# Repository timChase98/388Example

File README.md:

# ECE 388 Board Submission Standards

## Directory Layout
In the base Directory should be your Kicad project files and a directory called "renders" which contains the output files from your project. If you want to also version control your firmware (which you probably should) you can have a folder called "firmware" to manage code.  You must also have the gitignore that came with your repo.  

Your repo should be well maintained and updated regularly.  I should not just see a single commit titled "done".  You should be making frequent commits as you make changes to the status of your project.  You should also regularly push.

## README
The readme for your project should contain your project title, an overview of your project and any additionally relevant information. Images may go into the readmeimg folder. You must have the DRC badge present below your project title for submissions to be graded.

## Automated ERC and DRC Checks
Your repository has been configured to automatically run an ERC and DRC every time you push. Both of the ERC and DRC need to pass for a submission to be accepted. This will be signified by a green passing badge in the readme.

## Kicad Library
The whole class will share a kicad library on GitHub. The repo can be found [HERE](https://github.com/UmassD-ECE388/388Lib). You should fork this repo (information about forks [HERE](https://docs.github.com/en/github/collaborating-with-pull-requests/working-with-forks)), clone your fork onto your local machine and add both the symbol and footprints libraries to your library manager in Kicad.

From your project view select Preferences->Manage Symbol Libraries then click the add existing library button and navigate to where you cloned your fork of 388Lib to. Repeat these steps for Preferences->Manage Footprint Libraries

 Any symbols or footprints needed for your project need to be added to your local fork of the repo and shared with the class by submitting a pull request to the upstream repo. You are responsible for learning how to do this. There is plenty of documentation online (including some linked in this readme) about how to do this.

**ALL symbols and footprints used in your project need to be in the 388Lib repo before grading**

## Submissions
Submissions should be in the form of GitHub Releases.  When a deadline comes around whatever the latest release on your repo is will be taken as your submission.  You should not email me submissions, email submissions will not be graded.  Each submission must have a unique tag number starting X.00 where X is the number associated with the submission. When asked to resubmit you should increment the minor version number of the tag. EX if you just submitted with a tag of v1.00 the first resubmission should be tagged v1.01, the 10th resubmission would be v1.10. The hundredth submission should be taken as a sign that it's time revaluate some things.

Documentation on how to create a release can be found [HERE](https://docs.github.com/en/free-pro-team@latest/github/administering-a-repository/managing-releases-in-a-repository).

## Schematics Submission
You will create a release called "Schematic Submission" with an initial tag of v1.00

ERC must be run on all schematic before submission.  ERC errors will not only make your board not work, it will also make your design get rejected.  Schematics should be submitted as a PDF located in the "renders" folder.  To get Kicad to produce a PDF of your schematic select the plotter icon from the top menu and select the following settings.  

It's important that if you have more than one page that you select to export all pages.

## Bill Of Materials Submission
You will create a release titled "BOM Submission" with an initial tag of v2.00

We will be using [LCSC](https://lcsc.com) as our preferred supplier.  As such, all parts should be sourceable from LCSC unless previously discussed with myself.  Once submitted each group will meet with me for a Bill Of Materials (BOM) review.  BOM's should be exported from Kicad, then all additional data needs to be added. To do this in Eeschema go to Tools -> Generate Bill Of Materials and select bom2grouped_csv.  This will generate the BOM is Comma Separated Variable format.

After Kicad generates a BOM file you need to open it in a CSV editor of your choice, excel, open office, atom if you're a cool kid, vscode if you're a nerd, and patch in the additional data needed to submit.  This includes price breakdowns, LCSC part numbers and links.  An example is provided in this repository.  If a part is not available from LCSC and you have discussed this with me you can enter data into the OTHER SUPPLIER fields, otherwise they are unnecessary.  Note price breakdowns are for the cost of 1 part at the listed quantity, not the extended price.  

**BOMs That do not meet the format specification will be rejected** This means they must have all of the correct columns, in the correct order, with correct data in them, and be in **CSV** format.  

**All parts necessary for production of you board must be on the BOM** this included displays, connectors, wiring, etc.  If you need it for your board to be functional it needs to be on the BOM. Components that are not physical parts, ex mounting holes, fiducials, etc, should not be included.  

**We are ordering parts from LCSC.  BOMs that do not have LSCS part numbers will be rejected**

## Board Layout
It is important that the first thing you do when you start to layout your board is to setup your DRCs.  DRCs are the minimum checks you can do to make sure your board will have the possibility of being manufacturable.  They do not however verify your board will work correctly.  

We will be using JLCPCB's prototyping service for board production.  JLCPCB's design minimum design rules are located [HERE](https://jlcpcb.com/capabilities/Capabilities). **Some of these rules are different for different board configurations** unless you have specifically discussed with me your board will be 2 layer 1oz copper on 1.6mm FR-4.  Note these are minimums, not recommend values.  You should use Kicad's built-in circuit board calculator to come up with minimum for high power or critical traces.  All of these things need to be configured in the board setup dialog accessible via File -> Board Setup

It is also important to take note of silkscreen (called legend on the JLCPCB website) minimums.  A lot of standard libraries come with small text sizes and will need to be increased to pass DRC.  This can be done by setting the text properties in the Board Setup dialog.

Then going to Edit -> Text and Graphics properties and settings the following settings

Additionally it can be useful to have the help of the interactive router.  This is entirely up to personal preference, my preferred settings are shown below.  This dialog is accessible via the Route -> Interactive Router Settings menu.

Periodically while laying out your board you should run a DRC to verify there are no manufacturing issues. It is sometimes ok to wave DRC errors as Approved.  If there is an error that you believe should be waved discuss this with Dr. Viall or myself before continuing.

To verify you read this put a text file in the Renders folder titled "verification.txt" that contains the line "No Green M&M's were harmed in the production of this board" and nothing else.  Do not discuss this with requirement with other groups. 

## Board Submission
You will create a release called "Gerber Submission" with an initial tag of v3.00

DRC must be run on your board prior to submitting.  Any unapproved DRC errors will result in your design being rejected.  
**Boards with critical DRC errors are unmanufacturable**

**Boards must be clearly marked with identifying information** This includes the product name, Revision, Date, Lead layout engineer, all group members names, and the link to the project GitHub.  An Example from a Senior Design project is included below.  

**Boards must have Fiducials for automated assembly.** Submissions that do not have 1mm fiducials in the bottom left (FID1), Top Right (FID2), and Top Left (FID3) will be rejected. Note the ordering of the three fiducials is important for automated assembly. The area around fiducials should be clear of components that may interfere with automatic recognition (i.e. mounting holes, pin headers etc.) for at least 3mm from any edge of the copper center.  

Boards will be submitted in the form of gerber files located in the renders/gerbers directory.   

Directions to generate Gerber Files can be found [HERE](https://support.jlcpcb.com/article/149-how-to-generate-gerber-and-drill-files-in-kicad)

**You must generate both gerber and drill files to get your board manufactured**

## Board Population

In order to get a board assembled through the automated assembly process you must submit a finalized BOM that includes quantities and UUIDs from the stock sheet [HERE](https://docs.google.com/spreadsheets/d/1WtOakf2sV2Z24B9SvWYXxpJuLNhJUgvYpcEkdbbXuQU/edit#gid=0) and designators.  If a component is being sourced by you rather than a part that was ordered from the BOM you should put a "Y" in the self sourced column.  This file should only reflect components that need to be populated on the board.  i.e. resistors, caps, ICs, not mounting holes or solder jumpers.  An example of this is attached can be seen in this repo.  It should be named yourProjectName_assembly.csv and be in the base directory of your project when you create an assembly release.  Once you have submitted this file and your Kicad project files are in the repo you can schedule an appointment to get your board assembled.  

## Feedback

Feedback will be provided via Github Issues.  Changes that need to be made will be listed as a series of checkboxes on an issue.  These boxes should be checked off as they are completed.  You should have all of the boxes check before closing the issue to notify me that your submission needs to be reevaluated.  Any discussion about submissions should be done on the issue page.

**I can not recommend strongly enough that you have everything in as early as possible.  Your designs will likely get rejected the first time and you need time to be able to get a manufacturable board in before the deadline to order.**

## Relevant Links

[Layout Video](https://www.youtube.com/watch?v=Pfe_roicJkg)

[388Lib](https://github.com/UmassD-ECE388/388Lib)

[Stock Sheet](https://docs.google.com/spreadsheets/d/1WtOakf2sV2Z24B9SvWYXxpJuLNhJUgvYpcEkdbbXuQU/)

[PCB House](https://jlcpcb.com/)

[Component Supplier](https://lcsc.com/)

[AVR Hardware Implementation](http://ww1.microchip.com/downloads/en/AppNotes/AN2519-AVR-Microcontroller-Hardware-Design-Considerations-00002519B.pdf)

[AVR I2C](https://www.microchip.com/en-us/application-notes/an2480)

[NXP I2C Level Shifter](https://cdn-shop.adafruit.com/datasheets/an97055.pdf)

[TI Reverse Voltage Protection](https://www.ti.com/lit/an/slva139/slva139.pdf?ts=1632762332598&ref_url=https%253A%252F%252Fwww.google.com%252F)

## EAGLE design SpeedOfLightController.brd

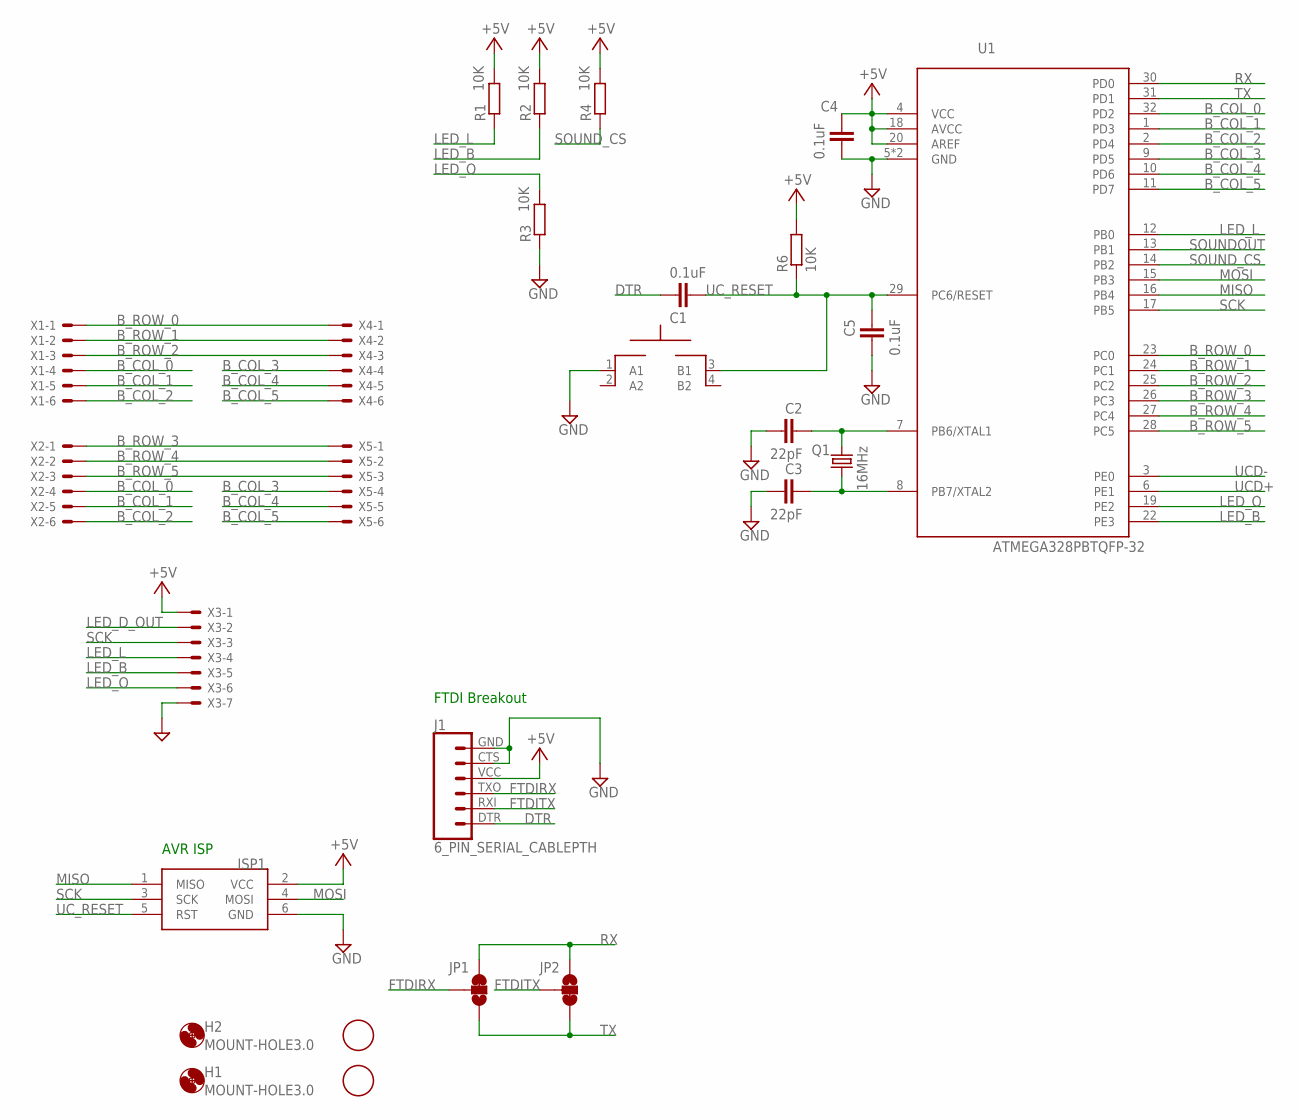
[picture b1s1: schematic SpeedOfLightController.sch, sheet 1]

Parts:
AF1, AF2: FIDUCIAL; FIDUCIAL_1MM
C1, C4, C5: 0.1uF; C0805
C2, C3: 22pF; C0805
H1, H2: MOUNT-HOLE3.0; 3,0
ISP1: AVRISP-6; AVRISP
J1: 6_PIN_SERIAL_CABLEPTH; FTDI_BASIC
JP1, JP2: JUMPER-SMT_3_1-NC_TRACE_SILK; SMT-JUMPER_3_1-NC_TRACE_SILK
Q1: 16MHz; HC49UP
R1, R2, R3, R4, R6: 10K; R0805
RESET: MOMENTARYBUTTON; SPST_NO_SMD
U1: ATMEGA328PBTQFP-32; QFP80P900X900X120-32N
X1, X2, X4, X5: JST-XH-06-PIN-LONG-PAD; JST-XH-06-PACKAGE-LONG-PAD
X3: JST-XH-07-PIN-LONG-PAD; JST-XH-07-PACKAGE-LONG-PAD

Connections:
+5V: C4.2, ISP1.2 (VCC), J1.VCC (4), R1.2, R2.2, R4.2, R6.2, U1.4 (VCC), U1.18 (AVCC), U1.20 (AREF), X3.1; also elsewhere on the board
B_COL_0: U1.32 (PD2), X1.4, X2.4
B_COL_1: U1.1 (PD3), X1.5, X2.5
B_COL_2: U1.2 (PD4), X1.6, X2.6
B_COL_3: U1.9 (PD5), X4.4, X5.4
B_COL_4: U1.10 (PD6), X4.5, X5.5
B_COL_5: U1.11 (PD7), X4.6, X5.6
B_ROW_0: U1.23 (PC0), X1.1, X4.1
B_ROW_1: U1.24 (PC1), X1.2, X4.2
B_ROW_2: U1.25 (PC2), X1.3, X4.3
B_ROW_3: U1.26 (PC3), X2.1, X5.1
B_ROW_4: U1.27 (PC4), X2.2, X5.2
B_ROW_5: U1.28 (PC5), X2.3, X5.3
DTR: C1.2, J1.DTR (1)
FTDIRX: J1.TXO (3), JP1.2
FTDITX: J1.RXI (2), JP2.2
GND: C2.1, C3.1, C4.1, C5.1, ISP1.6 (GND), J1.CTS (5), J1.GND (6), R3.1, RESET.1 (A1), U1.5 (GND), U1.21 (GND), X3.7; also elsewhere on the board
LED_B: R2.1, U1.22 (PE3), X3.5; also elsewhere on the board
LED_D_OUT: X3.2; also elsewhere on the board
LED_L: R1.1, U1.12 (PB0), X3.4; also elsewhere on the board
LED_O: R3.2, U1.19 (PE2), X3.6; also elsewhere on the board
MISO: ISP1.1 (MISO), U1.16 (PB4); also elsewhere on the board
MOSI: ISP1.4 (MOSI), U1.15 (PB3); also elsewhere on the board
unnamed: C2.2, Q1.1, U1.7 (PB6/XTAL1)
unnamed: C3.2, Q1.2, U1.8 (PB7/XTAL2)
RX: JP1.3, JP2.1, U1.30 (PD0)
SCK: ISP1.3 (SCK), U1.17 (PB5), X3.3; also elsewhere on the board
SOUNDOUT: U1.13 (PB1); also elsewhere on the board
SOUND_CS: R4.1, U1.14 (PB2); also elsewhere on the board
TX: JP1.1, JP2.3, U1.31 (PD1)
UCD+: U1.6 (PE1); also elsewhere on the board
UCD-: U1.3 (PE0); also elsewhere on the board
UC_RESET: C1.1, C5.2, ISP1.5 (RST), R6.1, RESET.3 (B1), U1.29 (PC6/RESET)

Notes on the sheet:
AVR ISP
FTDI Breakout

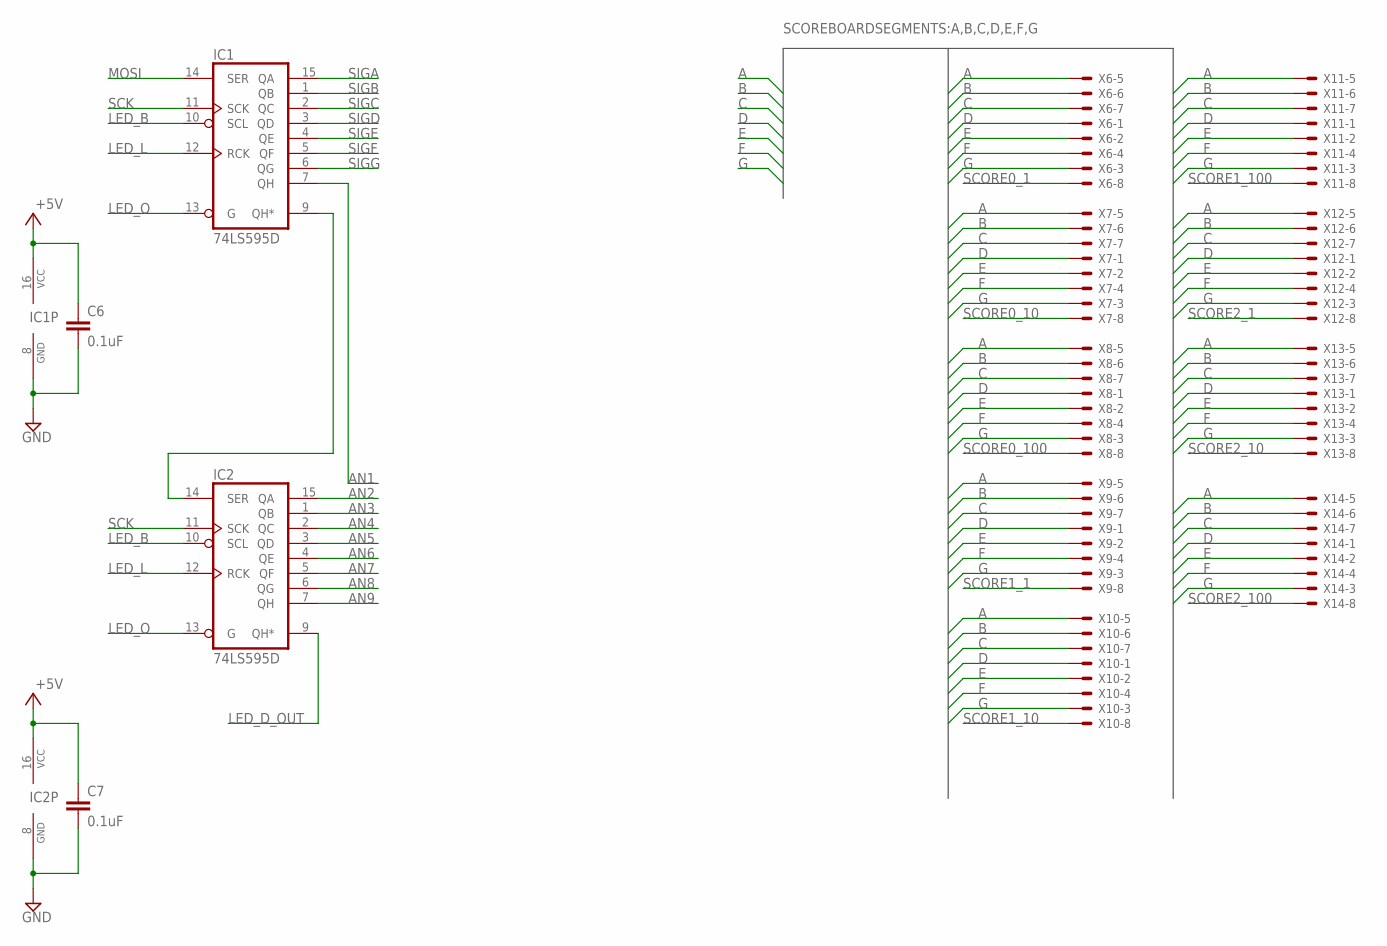
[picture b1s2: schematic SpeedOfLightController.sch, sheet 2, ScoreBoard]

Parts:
C6, C7: 0.1uF; C0805
IC1, IC2: 74LS595D; SO16
X6, X7, X8, X9, X10, X11, X12, X13, X14: JST-XH-08-PIN-LONG-PAD; JST-XH-08-PACKAGE-LONG-PAD

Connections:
+5V: C6.1, C7.1, IC1.16 (VCC), IC2.16 (VCC); also elsewhere on the board
A: X6.5, X7.5, X8.5, X9.5, X10.5, X11.5, X12.5, X13.5, X14.5; also elsewhere on the board
AN1: IC1.7 (QH); also elsewhere on the board
AN2: IC2.15 (QA); also elsewhere on the board
AN3: IC2.1 (QB); also elsewhere on the board
AN4: IC2.2 (QC); also elsewhere on the board
AN5: IC2.3 (QD); also elsewhere on the board
AN6: IC2.4 (QE); also elsewhere on the board
AN7: IC2.5 (QF); also elsewhere on the board
AN8: IC2.6 (QG); also elsewhere on the board
AN9: IC2.7 (QH); also elsewhere on the board
B: X6.6, X7.6, X8.6, X9.6, X10.6, X11.6, X12.6, X13.6, X14.6; also elsewhere on the board
C: X6.7, X7.7, X8.7, X9.7, X10.7, X11.7, X12.7, X13.7, X14.7; also elsewhere on the board
D: X6.1, X7.1, X8.1, X9.1, X10.1, X11.1, X12.1, X13.1, X14.1; also elsewhere on the board
E: X6.2, X7.2, X8.2, X9.2, X10.2, X11.2, X12.2, X13.2, X14.2; also elsewhere on the board
F: X6.4, X7.4, X8.4, X9.4, X10.4, X11.4, X12.4, X13.4, X14.4; also elsewhere on the board
G: X6.3, X7.3, X8.3, X9.3, X10.3, X11.3, X12.3, X13.3, X14.3; also elsewhere on the board
GND: C6.2, C7.2, IC1.8 (GND), IC2.8 (GND); also elsewhere on the board
LED_B: IC1.10 (SCL), IC2.10 (SCL); also elsewhere on the board
LED_D_OUT: IC2.9 (QH*); also elsewhere on the board
LED_L: IC1.12 (RCK), IC2.12 (RCK); also elsewhere on the board
LED_O: IC1.13 (G), IC2.13 (G); also elsewhere on the board
MOSI: IC1.14 (SER); also elsewhere on the board
unnamed: IC1.9 (QH*), IC2.14 (SER)
SCK: IC1.11 (SCK), IC2.11 (SCK); also elsewhere on the board
SCORE0_1: X6.8; also elsewhere on the board
SCORE0_10: X7.8; also elsewhere on the board
SCORE0_100: X8.8; also elsewhere on the board
SCORE1_1: X9.8; also elsewhere on the board
SCORE1_10: X10.8; also elsewhere on the board
SCORE1_100: X11.8; also elsewhere on the board
SCORE2_1: X12.8; also elsewhere on the board
SCORE2_10: X13.8; also elsewhere on the board
SCORE2_100: X14.8; also elsewhere on the board
SIGA: IC1.15 (QA); also elsewhere on the board
SIGB: IC1.1 (QB); also elsewhere on the board
SIGC: IC1.2 (QC); also elsewhere on the board
SIGD: IC1.3 (QD); also elsewhere on the board
SIGE: IC1.4 (QE); also elsewhere on the board
SIGF: IC1.5 (QF); also elsewhere on the board
SIGG: IC1.6 (QG); also elsewhere on the board

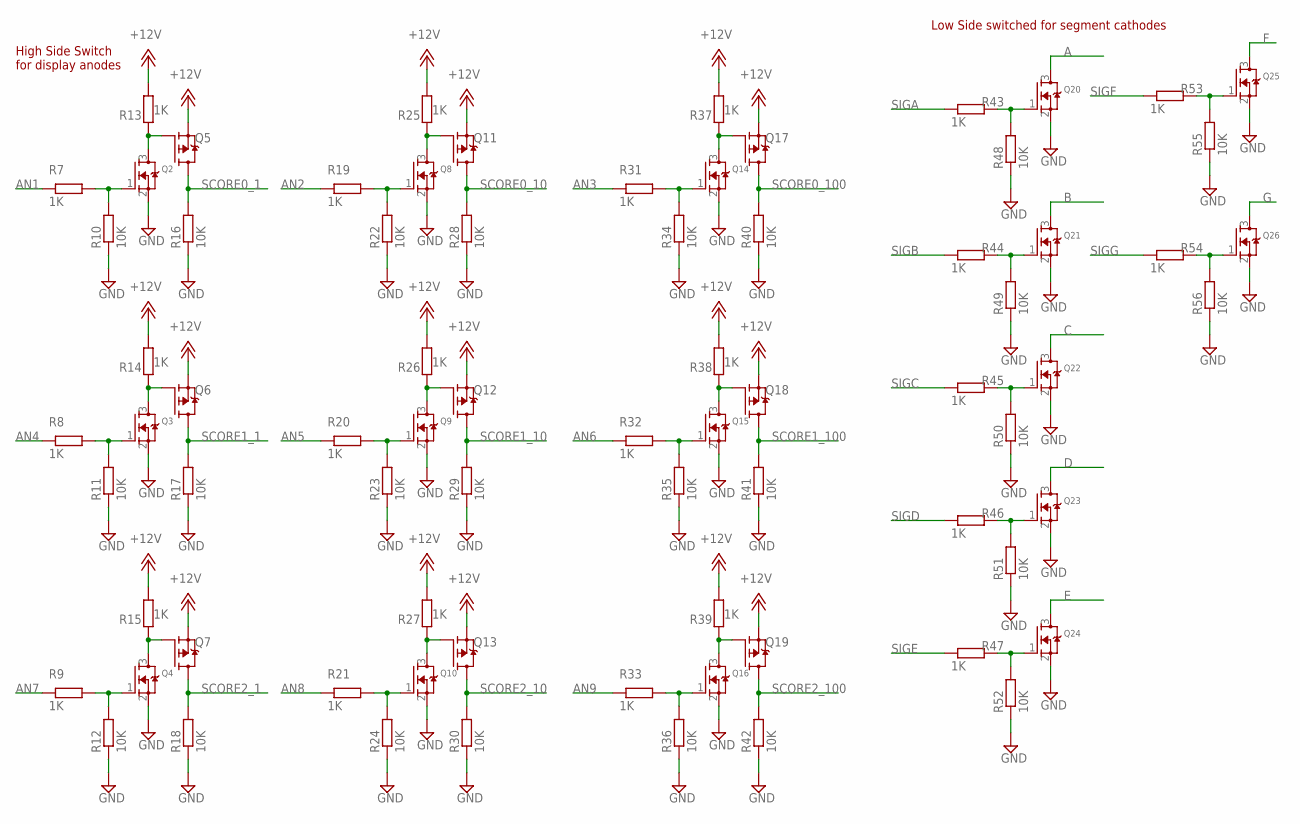
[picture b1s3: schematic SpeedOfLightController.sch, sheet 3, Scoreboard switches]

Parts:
Q2, Q3, Q4, Q8, Q9, Q10, Q14, Q15, Q16, Q20, Q21, Q22, Q23, Q24, Q25, Q26: AO3414SOT23; SOT95P240X110-3N
Q5, Q6, Q7, Q11, Q12, Q13, Q17, Q18, Q19: AO3415; SOT95P240X110-3N
R7, R8, R9, R13, R14, R15, R19, R20, R21, R25, R26, R27, R31, R32, R33, R37, R38, R39, R43, R44, R45, R46, R47, R53, R54: 1K; R0805
R10, R11, R12, R16, R17, R18, R22, R23, R24, R28, R29, R30, R34, R35, R36, R40, R41, R42, R48, R49, R50, R51, R52, R55, R56: 10K; R0805

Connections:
+12V: Q5.2 (S), Q6.2 (S), Q7.2 (S), Q11.2 (S), Q12.2 (S), Q13.2 (S), Q17.2 (S), Q18.2 (S), Q19.2 (S), R13.2, R14.2, R15.2, R25.2, R26.2, R27.2, R37.2, R38.2, R39.2; also elsewhere on the board
A: Q20.3 (D); also elsewhere on the board
AN1: R7.1; also elsewhere on the board
AN2: R19.1; also elsewhere on the board
AN3: R31.1; also elsewhere on the board
AN4: R8.1; also elsewhere on the board
AN5: R20.1; also elsewhere on the board
AN6: R32.1; also elsewhere on the board
AN7: R9.1; also elsewhere on the board
AN8: R21.1; also elsewhere on the board
AN9: R33.1; also elsewhere on the board
B: Q21.3 (D); also elsewhere on the board
C: Q22.3 (D); also elsewhere on the board
D: Q23.3 (D); also elsewhere on the board
E: Q24.3 (D); also elsewhere on the board
F: Q25.3 (D); also elsewhere on the board
G: Q26.3 (D); also elsewhere on the board
GND: Q2.2 (S), Q3.2 (S), Q4.2 (S), Q8.2 (S), Q9.2 (S), Q10.2 (S), Q14.2 (S), Q15.2 (S), Q16.2 (S), Q20.2 (S), Q21.2 (S), Q22.2 (S), Q23.2 (S), Q24.2 (S), Q25.2 (S), Q26.2 (S), R10.1, R11.1, R12.1, R16.1, R17.1, R18.1, R22.1, R23.1, R24.1, R28.1, R29.1, R30.1, R34.1, R35.1, R36.1, R40.1, R41.1, R42.1, R48.1, R49.1, R50.1, R51.1, R52.1, R55.1, R56.1; also elsewhere on the board
unnamed: Q21.1 (G), R44.2, R49.2
unnamed: Q22.1 (G), R45.2, R50.2
unnamed: Q23.1 (G), R46.2, R51.2
unnamed: Q24.1 (G), R47.2, R52.2
unnamed: Q20.1 (G), R43.2, R48.2
unnamed: Q25.1 (G), R53.2, R55.2
unnamed: Q26.1 (G), R54.2, R56.2
unnamed: Q2.1 (G), R7.2, R10.2
unnamed: Q8.1 (G), R19.2, R22.2
unnamed: Q14.1 (G), R31.2, R34.2
unnamed: Q3.1 (G), R8.2, R11.2
unnamed: Q9.1 (G), R20.2, R23.2
unnamed: Q15.1 (G), R32.2, R35.2
unnamed: Q4.1 (G), R9.2, R12.2
unnamed: Q10.1 (G), R21.2, R24.2
unnamed: Q16.1 (G), R33.2, R36.2
unnamed: Q16.3 (D), Q19.1 (G), R39.1
unnamed: Q10.3 (D), Q13.1 (G), R27.1
unnamed: Q4.3 (D), Q7.1 (G), R15.1
unnamed: Q3.3 (D), Q6.1 (G), R14.1
unnamed: Q9.3 (D), Q12.1 (G), R26.1
unnamed: Q15.3 (D), Q18.1 (G), R38.1
unnamed: Q14.3 (D), Q17.1 (G), R37.1
unnamed: Q8.3 (D), Q11.1 (G), R25.1
unnamed: Q2.3 (D), Q5.1 (G), R13.1
SCORE0_1: Q5.3 (D), R16.2; also elsewhere on the board
SCORE0_10: Q11.3 (D), R28.2; also elsewhere on the board
SCORE0_100: Q17.3 (D), R40.2; also elsewhere on the board
SCORE1_1: Q6.3 (D), R17.2; also elsewhere on the board
SCORE1_10: Q12.3 (D), R29.2; also elsewhere on the board
SCORE1_100: Q18.3 (D), R41.2; also elsewhere on the board
SCORE2_1: Q7.3 (D), R18.2; also elsewhere on the board
SCORE2_10: Q13.3 (D), R30.2; also elsewhere on the board
SCORE2_100: Q19.3 (D), R42.2; also elsewhere on the board
SIGA: R43.1; also elsewhere on the board
SIGB: R44.1; also elsewhere on the board
SIGC: R45.1; also elsewhere on the board
SIGD: R46.1; also elsewhere on the board
SIGE: R47.1; also elsewhere on the board
SIGF: R53.1; also elsewhere on the board
SIGG: R54.1; also elsewhere on the board

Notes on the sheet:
High Side Switch for display anodes
Low Side switched for segment cathodes

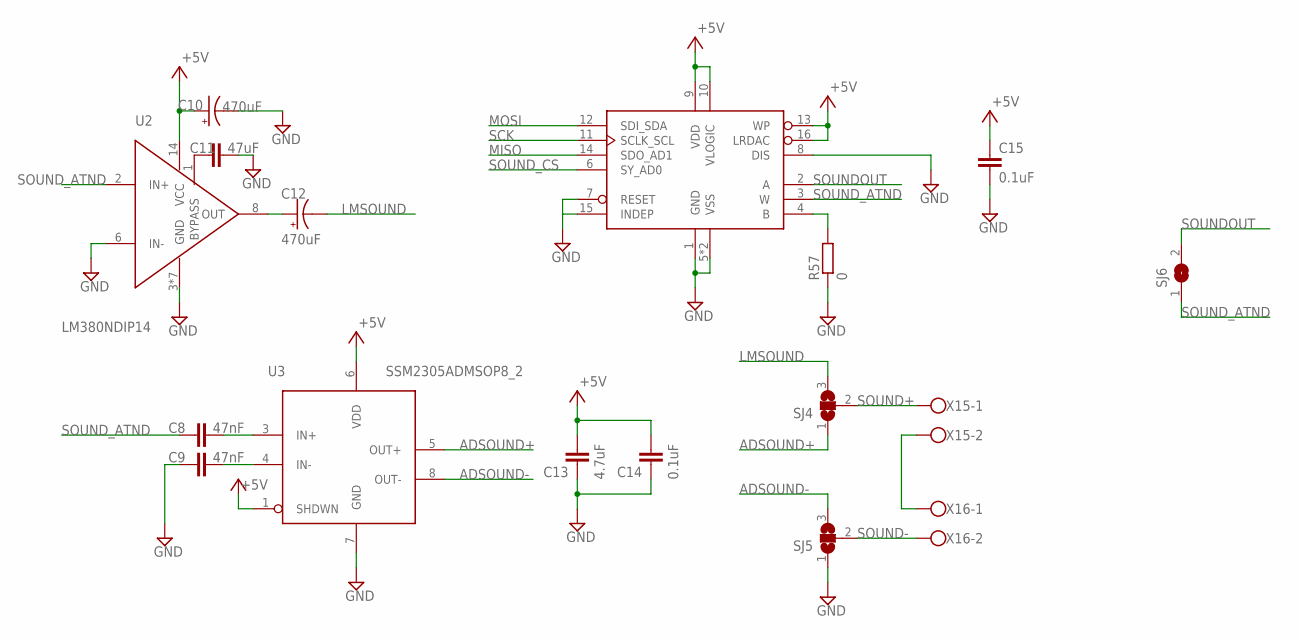
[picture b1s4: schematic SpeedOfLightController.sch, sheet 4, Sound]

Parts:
C8, C9: 47nF; C0805
C10, C12: 470uF; 140CLH-0810
C11: 47uF; C0805
C13: 4.7uF; C0805
C14, C15: 0.1uF; C0805
R57: 0; R0805W
SJ4, SJ5: SJ2W; SJ_2
SJ6: SJ
U2: LM380NDIP14; DIP762W53P254L1969H508Q14B
U3: SSM2305ADMSOP8_2; SOP65P490X95-8N
U4: AD5141ADLFCSP3; QFN50P300X300X80-17T160N
X15, X16: 1X02_5MM_SCREW; W237-102

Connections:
+5V: C10.+, C13.2, C14.2, C15.1, U2.14 (VCC), U3.1 (SHDWN), U3.6 (VDD), U4.9 (VDD), U4.10 (VLOGIC), U4.13 (WP), U4.16 (LRDAC); also elsewhere on the board
ADSOUND+: SJ4.1, U3.5 (OUT+)
ADSOUND-: SJ5.3, U3.8 (OUT-)
GND: C9.1, C10.-, C11.2, C13.1, C14.1, C15.2, R57.1, SJ5.1, U2.3 (GND), U2.4 (GND), U2.5 (GND), U2.6 (IN-), U2.7 (GND), U2.10 (GND), U2.11 (GND), U2.12 (GND), U3.7 (GND), U4.1 (GND), U4.5 (VSS), U4.7 (RESET), U4.8 (DIS), U4.15 (INDEP), U4.17 (VSS); also elsewhere on the board
LMSOUND: C12.-, SJ4.3
MISO: U4.14 (SDO_AD1); also elsewhere on the board
MOSI: U4.12 (SDI_SDA); also elsewhere on the board
unnamed: X15.2, X16.1
unnamed: C12.+, U2.8 (OUT)
unnamed: C11.1, U2.1 (BYPASS)
unnamed: C9.2, U3.4 (IN-)
unnamed: C8.2, U3.3 (IN+)
unnamed: R57.2, U4.4 (B)
SCK: U4.11 (SCLK_SCL); also elsewhere on the board
SOUND+: SJ4.2, X15.1
SOUND-: SJ5.2, X16.2
SOUNDOUT: SJ6.2, U4.2 (A); also elsewhere on the board
SOUND_ATND: C8.1, SJ6.1, U2.2 (IN+), U4.3 (W)
SOUND_CS: U4.6 (SY_AD0); also elsewhere on the board

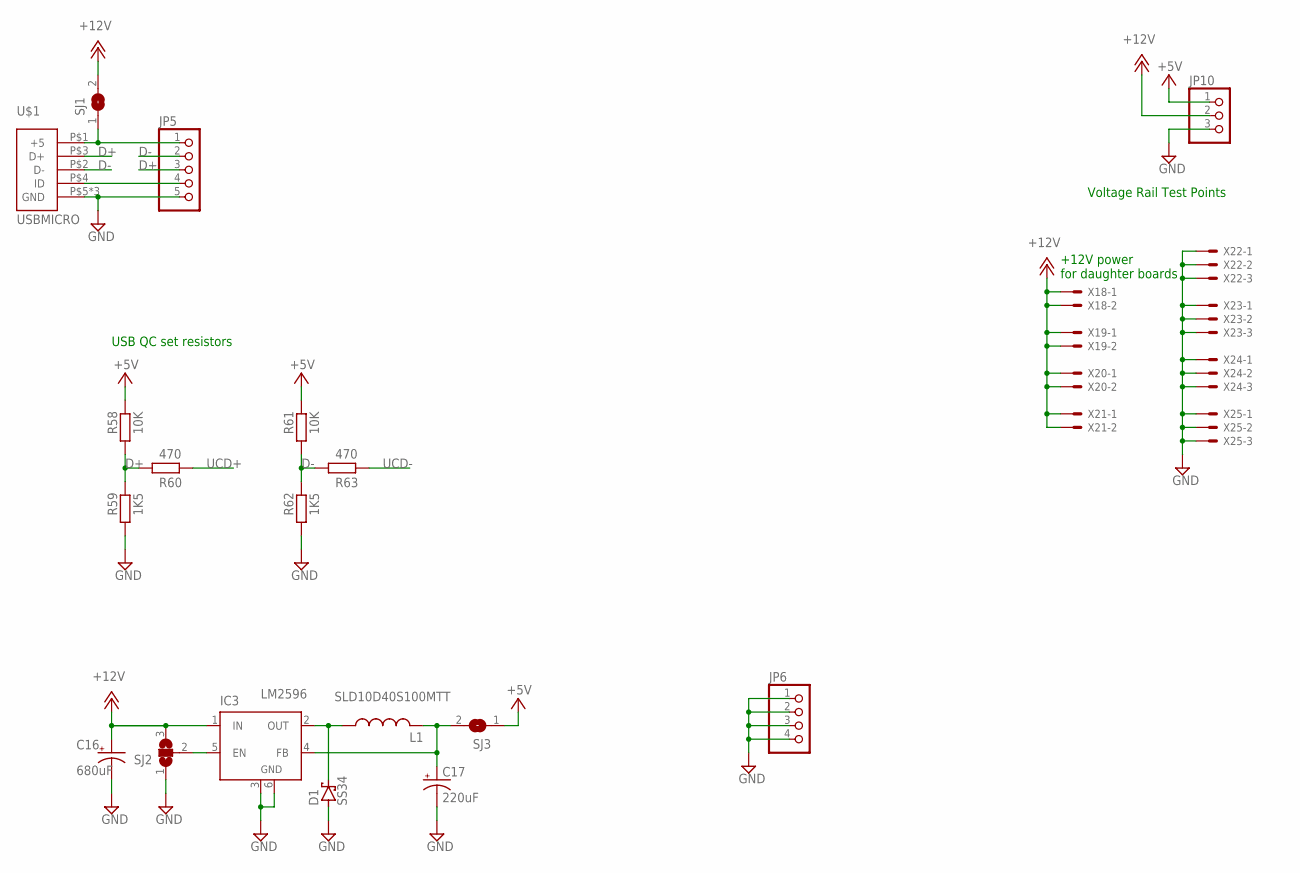
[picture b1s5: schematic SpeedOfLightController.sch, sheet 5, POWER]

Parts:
C16: 680uF; 140CLH-0810
C17: 220uF; 140CLH-0810
D1: SS34; SMA
IC3: LM2596S; TO263-5
JP5: PINHD-1X5; 1X05
JP6: PINHD-1X4; 1X04
JP10: PINHD-1X3; 1X03
L1: SLD10D40S100MTT; SMD10.5X10.3
R58, R61: 10K; R0805
R59, R62: 1K5; R0805
R60, R63: 470; R0805
SJ1, SJ3: SJ
SJ2: SJ2WW; SJ_2W
U$1: USBMICRO
X18, X19, X20, X21: JST-XH-02-PIN-LONG-PAD; JST-XH-02-PACKAGE-LONG-PAD
X22, X23, X24, X25: JST-XH-03-PIN-LONG-PAD; JST-XH-03-PACKAGE-LONG-PAD

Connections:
+5V: JP10.1, R58.2, R61.1, SJ3.1; also elsewhere on the board
+12V: C16.+, IC3.1 (IN), JP10.2, SJ1.2, SJ2.3, X18.1, X18.2, X19.1, X19.2, X20.1, X20.2, X21.1, X21.2; also elsewhere on the board
D+: JP5.3, R58.1, R59.2, R60.2, U$1.P$3 (D+)
D-: JP5.2, R61.2, R62.1, R63.1, U$1.P$2 (D-)
GND: C16.-, C17.-, D1.A, IC3.3 (GND), IC3.6 (GND), JP5.5, JP6.1, JP6.2, JP6.3, JP6.4, JP10.3, R59.1, R62.2, SJ2.1, U$1.P$5 (GND), U$1.P$6 (GND), U$1.P$8 (GND), X22.1, X22.2, X22.3, X23.1, X23.2, X23.3, X24.1, X24.2, X24.3, X25.1, X25.2, X25.3; also elsewhere on the board
unnamed: JP5.1, SJ1.1, U$1.P$1 (+5)
unnamed: JP5.4, U$1.P$4 (ID)
unnamed: D1.C, IC3.2 (OUT), L1.P$1 (1)
unnamed: IC3.5 (EN), SJ2.2
unnamed: C17.+, IC3.4 (FB), L1.P$2 (2), SJ3.2
UCD+: R60.1; also elsewhere on the board
UCD-: R63.2; also elsewhere on the board

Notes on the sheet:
Voltage Rail Test Points
+12V power for daughter boards
USB QC set resistors
LM2596

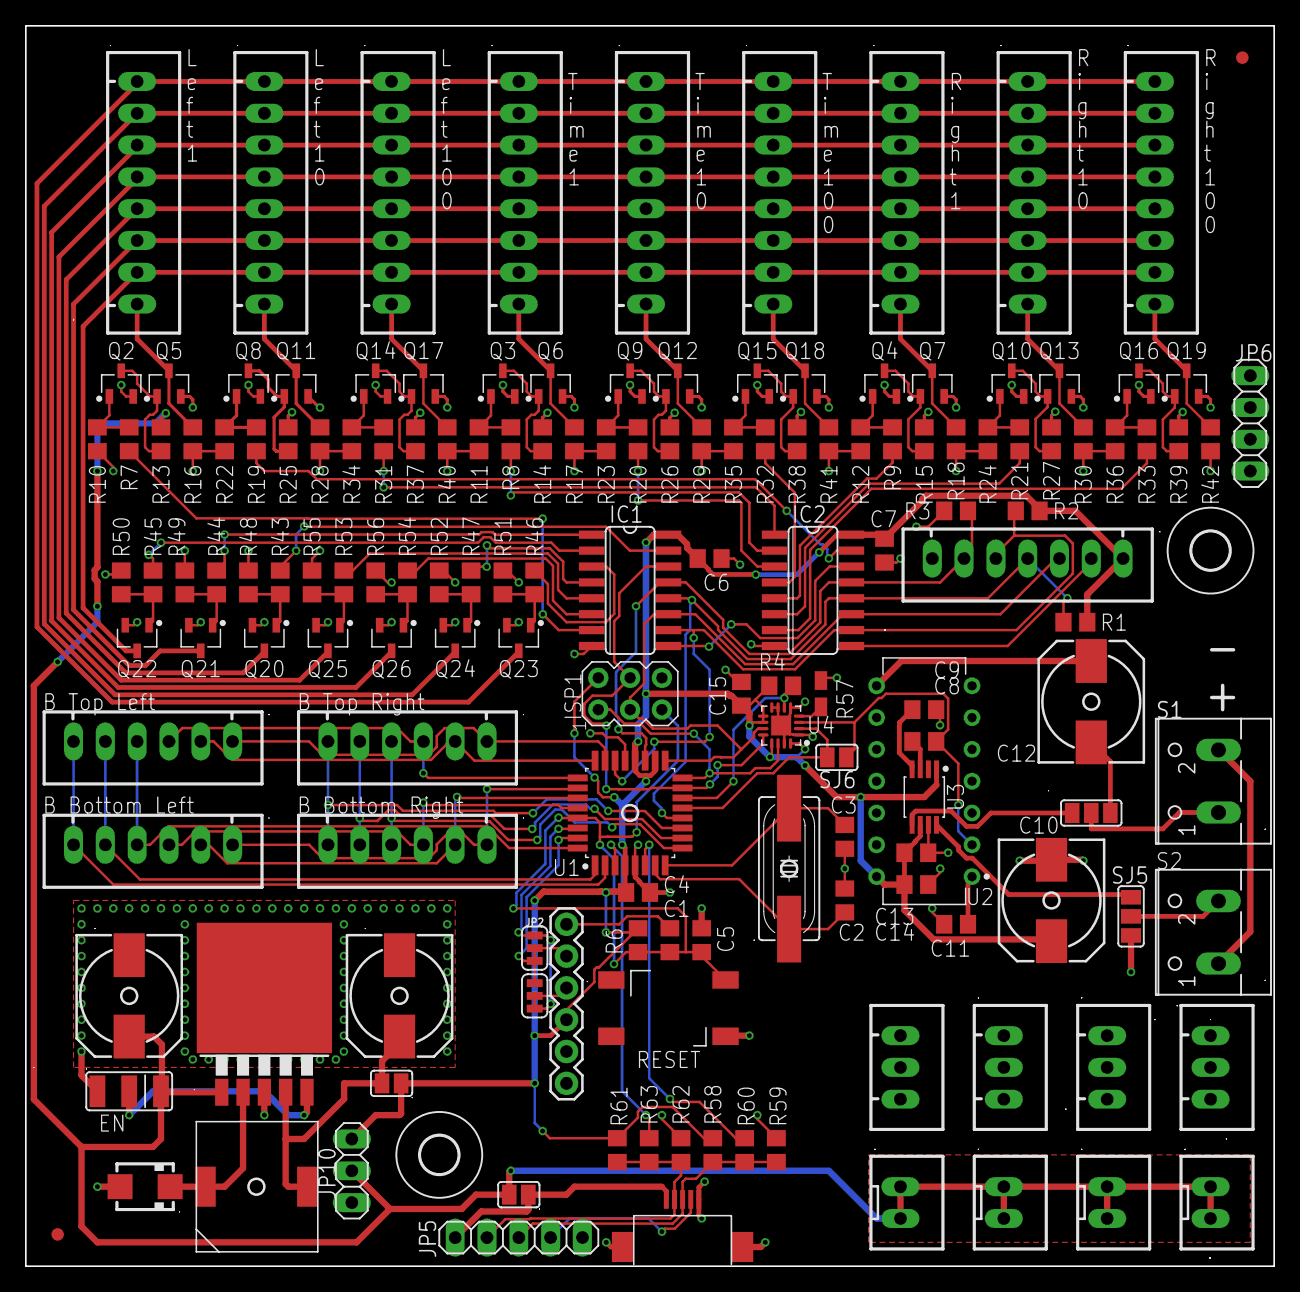
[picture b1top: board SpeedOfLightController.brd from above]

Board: 2 copper layers, 99.7 x 99.1 mm, 157 parts (0 on the bottom side), 111 nets.

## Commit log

2021-09-09 Changed to Kicad
2021-09-24 Removed Eagele Files
2021-09-24 added missing picture for kicad lib manager
2021-09-25 Fixed formating issue
2021-09-27 Added Links
2021-09-28 added renders schematic
2021-10-05 Added Example BOM

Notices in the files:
parts and their libraries:
SparkFun-Jumpers: Licensing: Creative Commons ShareAlike 4.0 International - https://creativecommons.org/licenses/by-sa/4.0
